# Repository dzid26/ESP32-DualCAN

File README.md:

# ESP32-DualCAN - aka Dorky Commander
Open source alternative to S3XY Commander with Molex connector compatible with Enhauto harnesses.

ESP32-C6 functions: 
- Dual CAN
- BLE for WebUI, OTA and TeslaBLE
- WiFi (file browser)
- USB-C for development (flashing, debugging)

See [`hardware/README.md`](hardware/README.md) for detailed spec and schematics.

## Flash the firmware

### Option A: Web UI (wireless OTA update)

1. Connect via BLE (see [Connect over BLE](#connect-over-ble)).
2. Go to **Settings → Firmware** in the [Dorky Commander web UI](https://opencartools.github.io/ESP32-DualCAN/).
3. Click **Upload .bin** and select a firmware `.bin` from disk (download from [GitHub Releases](https://github.com/opencartools/ESP32-DualCAN/releases) if needed).
4. The progress bar shows transfer status. The device reboots automatically when done.

### Option B: USB

**Download prebuilt binary:**

1. Download the latest `dorky-commander-vX.Y.Z.bin` from [GitHub Releases](https://github.com/opencartools/ESP32-DualCAN/releases).
2. Connect the board via USB-C. Easiest: open the [Espressif Web Flasher](https://espressif.github.io/esptool-js/) in Chrome and flash the `.bin` — no install needed.

   CLI alternative:

   ```bash
   pip install esptool
   esptool.py --chip esp32c6 write_flash 0x10000 dorky-commander-vX.Y.Z.bin
   ```

To build from source, see [firmware/README.md — Development — Build & Flash](firmware/README.md#build--flash) (PlatformIO extension recommended).

---

## Connect over BLE

1. Open the [Dorky Commander web UI](https://opencartools.github.io/ESP32-DualCAN/) in Chrome.
   *(Or install it as an app: Settings → Install app → Add to home screen.)*
2. Click **Connect** in the status bar.
3. Select **Dorky Commander** from the Bluetooth pairing dialog.
4. The status bar turns green and shows the firmware version.

> [!NOTE]
> The board advertises as `Dorky Commander`. Once paired, the pairing window stays closed for security — new devices cannot pair until you re-open it with a short-press of the B button or from the web UI on a bonded device (**Settings → Bluetooth → Open pairing window**). 

### "B" button — Bluetooth / Factory Reset

| Press | Action |
|---|---|
| Short press — release within 15 s | Open BLE pairing window for 60 s - see below |
| Hold ≥15 s | Factory reset — wipes BLE bonds, credentials, and scripts |
| Hold on Reset | ESP32 boot mode (advanced) |

## "R" button - Reset

ESP32 reset.

> [!TIP]
> If the board will be hidden behind car trim, pair with at least two devices (e.g., phone + laptop) — this avoids needing to reach the button, in case you loose a bond with the device.

See [docs/ble.md](docs/ble.md) for the full flow and troubleshooting.

---

## Choose your car

The board needs signal definitions (CAN dbc) to interpret signal `DI_vehicleSpeed` to raw IDs.

- Click the **car icon** in the top status bar and pick your vehicle (e.g., Tesla Model 3/Y). The matching DBC(s) load automatically.
- Or open **Gallery → DBCs** and click **Load** on the card for your car (choose **Bus 0** or **Bus 1** with the selector on the card if needed).
- For a custom file, open **DBC** in the left rail and click **Upload .dbc** — use the **Bus 0 / Bus 1** tabs at the top to view what's loaded for each bus.

The browser keeps the DBC locally in the browser for autocomplete and for preprocessing signal names into numeric IDs when you save a script. Verify with the search box in the DBC view.

---

## Install a script

1. Open **Gallery** in the left rail → **Scripts** tab.
2. Find **Hello log** and click **Install** — it opens **Automations** with the file preloaded (or use **Automations → Load… → Hello log**).
3. Click **Save & enable** (or **Save** then toggle). The file appears in the **Installed** list on the left; the switch shows enabled/disabled. Use **Revert** to discard edits.
4. With the script enabled, open **Log** (left rail, bottom) — you should see `hello_log: setup` followed by `heartbeat` every 5 s. `print()` from the board streams there over BLE; no CAN connection required.

5. Next, try more useful script from the **Gallery** — browse **Gallery → Scripts** for real-car automations like *Easy entry window drop*, or *Light flash → horn beep*, or pick a DBC in **Gallery → DBCs**.

---

## Use action tiles

1. Open **Gallery** in the left rail → **Scripts** tab.
2. Find **Tesla fold mirrors** and click **Install** — it opens **Automations** with `tesla_fold_mirror_tile.be` preloaded. Click **Save & enable**.
3. Return to **Dashboard**: two tiles appear — `fold_mirrors` and `unfold_mirrors`.
4. Tap a tile — the mirrors fold/unfold and the LED blinks blue. Requires Tesla Model 3/Y DBC on Bus 0 and the car awake.

## Use AI edit to write simple scripts

No coding needed — describe what you want in plain English.

1. One-time setup: Open **Settings → AI assistant** and paste your Anthropic API key — **BYOK** (Bring Your Own Key, billed to your Anthropic account). The key is stored locally in your browser and, if you click **Save to device**, also on the Dorky Commander non-volatile-storage - so any paired browser can reuse it. The browser calls Anthropic directly (`api.anthropic.com`); the key is never shared - it stays with you.

2. **Option A — from a script:** Open **Automations**, then click **AI edit** (sparkle icon) on any script. It opens **AI assistant** with that file attached as context — just type what to change.
   **Option B — from scratch:** Open **AI assistant** in the left rail directly and type a request, e.g., `Print battery temperature to log panel`

3. Press **Send** (`Ctrl/Cmd+Enter`). The assistant streams a `berry` code block (knowing your loaded DBC signals) with a proper `# @name` and `def setup()`.

4. Click **Install & enable** on the code card — it saves as `ai_script_*.be` and enables it. Check **Log** for `print()` output or **Dashboard** if it registered an action tile.

> [!TIP]
> Load a CAN definitions first (Choose your car) — the AI sees the first ~80 signal names from the browser and will use exact `message_name` / `signal_name` in `msg_sig_get`.

---

## Write your own scripts

Ready to go beyond examples?

- In **Automations**, click **Scripting Guide** (top bar, next to **New** / **Load…**) — it opens `docs/scripting.md` inside the UI with the full Berry API, CAN/DBC, timers, actions, LED, and `state_*` storage, plus a syntax cheat sheet. No tab switching needed. Point your AI agents to `docs/scripting.md` to help you out.

Start small: copy a Gallery script, tweak it in the editor, **Save & enable**, and watch **Log**.

---

## Development

### Brand scripting — adding scripts to the Gallery

See [`scripts/README.md`](scripts/README.md) for the full guide — Gallery pulls from `scripts/<brand>/*.be` at npm build time (`import.meta.glob`). Create `scripts/<brand>/your_script.be` with `# @name` / `# @description` / `# @bus` file header, implement `def setup()`, and verify in **Gallery → Scripts → Install**.

### Firmware

See [firmware/README.md — Development](firmware/README.md#development) for build, flash, and test instructions. Recommended: [PlatformIO IDE extension for VS Code](https://platformio.org/install).

### Web UI

First time
```bash
cd webui
npm install
```
Then
```
npm run dev   # open http://localhost:5173
```

Requires [Node.js](https://nodejs.org/).

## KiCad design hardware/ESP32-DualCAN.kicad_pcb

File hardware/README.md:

# Hardware — ESP32-DualCAN

## Characteristics
- 9-58 V operating range (e.g. Cybertruck),
- 5V rail: 0.5A continuous at room temp
- Dual CAN
- integrated 2.4 GHz antenna
- RGB LED
- USB-C - USB CDC (virtual COM, debugging)  

## Case
Designed in FreeCAD
- size 23.5 x 42.8 x 12.3 mm

## ICs
- ESP32-C6-Zero (ESP32-C6FH8, 8MB, BLE + WiFi, 2x TWAI CAN2.0 controllers)
- 2x CAN transceivers TCAN1044
- TI LV2862 DC/DC converter

## PCB
Designed in Kicad
- size 19.5 x 41.5 mm

## Images
- ESP32-C6-Zero chiplet and Molex connector:

- On the other side there are components and optional pads to solder cables with a female [connector](https://duckduckgo.com/?q=MX2.54+cable+6p) to daisy chain with s3xy buttons or a strip:

- It can accommodate optional female 2.54mm headers for custom extensions:

## Schematic

Source files: [`ESP32-DualCAN.kicad_sch`](ESP32-DualCAN.kicad_sch), [`ESP32-DualCAN.kicad_pcb`](ESP32-DualCAN.kicad_pcb) — see [KiCad-Waveshare-ESP32/](KiCad-Waveshare-ESP32/) for the ESP32-C6-Zero module footprint.

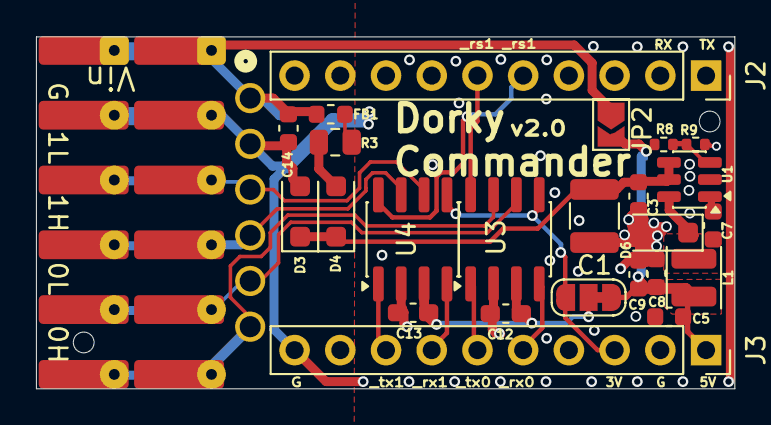
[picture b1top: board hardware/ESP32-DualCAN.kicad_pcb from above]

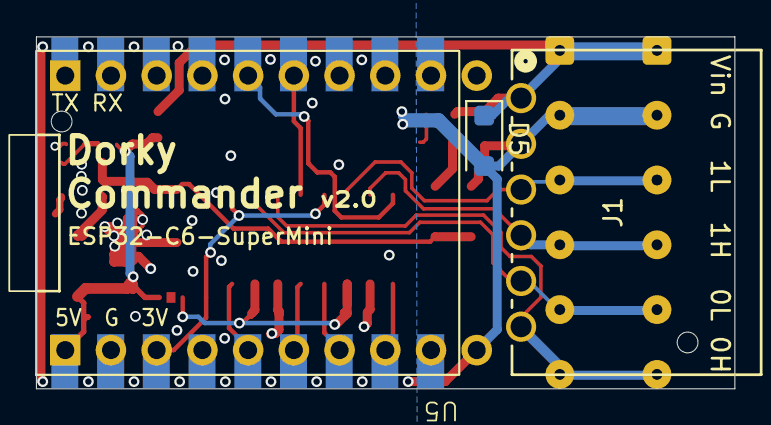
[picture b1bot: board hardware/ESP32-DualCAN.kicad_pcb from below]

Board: 2 copper layers, 38.8 x 19.6 mm, 31 parts (3 on the bottom side), 30 nets.

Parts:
C1: 10u 100v; C_1210_3225Metric
C3, C14: 100n 100V; C_0603_1608Metric
C5, C9: 22u; C_0603_1608Metric
C7, C8: 100n; C_0603_1608Metric
C12, C13: 100n; C_0603_1608Metric_Pad1.08x0.95mm_HandSolder
D3, D6: DSK38; D_SOD-123F
D4: SMF58A; D_SOD-123F
D5: SMF30CA; D_SOD-123F
FB1: FerriteBead; L_0603_1608Metric
J1: Molex 70553 6p; CONN_705530005_06_MOL
J2, J3: Conn_01x10_Socket; PinSocket_1x10_P2.54mm_Vertical
J4, J6: holes; SolderWire-0.1sqmm_1x06_P3.6mm_D0.4mm_OD1mm
J5, J7: pads; SolderWire-0.1sqmm_1x06_P3.6mm_D0.4mm_OD1mm
JP1: SolderJumper_3_Bridged12; SolderJumper-3_P1.3mm_Bridged12_RoundedPad1.0x1.5mm_NumberL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
JP2: SolderJumper_2_Open; SolderJumper-2_P1.3mm_Open_TrianglePad1.0x1.5mm
L1: 22uH; L_Changjiang_FTC322520S
R3: 1ohm; R_0805_2012Metric
R8: 56k; R_0402_1005Metric
R9: 10k; R_0402_1005Metric
U1: MLMR16006Y; TSOT-23-6
U3, U4: TCAN1044AV; SOIC-8_3.9x4.9mm_P1.27mm
U5: ESP32-C6-Zero; Waveshare-ESP32-C6-Zero

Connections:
+3.3V: J3.3, JP1.3 (B), U3.5 (VIO), U4.5 (VIO), U5.3 (V3V)
+BATT: C14.1, D5.1 (A1), FB1.1, J1.1, J4.1, J5.1, J6.1, J7.1, JP2.1 (A)
/BATT_Diode: C1.1, C3.1, D3.1 (K), D4.1 (A1), U1.4 (EN), U1.5 (VIN)
CAN0_H: J1.6, J4.6, J5.6, J6.6, J7.6, U3.7 (CANH)
CAN0_L: J1.5, J4.5, J5.5, J6.5, J7.5, U3.6 (CANL)
CAN0_RS: J2.6, U3.8 (STB), U5.13 (IO19)
CAN0_RXD: J3.5, U3.4 (RXD), U5.5 (IO1)
CAN0_TXD: J3.6, U3.1 (TXD), U5.6 (IO2)
CAN1_H: J1.4, J4.4, J5.4, J6.4, J7.4, U4.7 (CANH)
CAN1_L: J1.3, J4.3, J5.3, J6.3, J7.3, U4.6 (CANL)
CAN1_RS: J2.5, U4.8 (STB), U5.14 (IO18)
CAN1_RXD: J3.7, U4.4 (RXD), U5.7 (IO3)
CAN1_TXD: J3.8, U4.1 (TXD), U5.8 (IO4)
GND: C1.2, C3.2, C5.2, C8.2, C9.2, C12.2, C13.2, C14.2, D4.2 (A2), D5.2 (A2), D6.2 (A), J1.2, J3.2, J3.10, J4.2, J5.2, J6.2, J7.2, R9.1, U1.2 (GND), U3.2 (GND), U4.2 (GND), U5.2 (GND)
unnamed: D3.2 (A), R3.2
unnamed: C7.2, D6.1 (K), L1.1, U1.6 (SW)
unnamed: FB1.2, R3.1
unnamed: J2.1, U5.18 (TX)
unnamed: J2.2, U5.17 (RX)
unnamed: J2.3, U5.16 (IO14)
unnamed: J2.4, U5.15 (IO15)
unnamed: J2.7, U5.12 (IO20)
unnamed: J2.8, U5.11 (IO21)
unnamed: J2.9, U5.10 (IO22)
unnamed: J3.4, U5.4 (IO0)
unnamed: J3.9, U5.9 (IO5)
unnamed: C12.1, C13.1, JP1.2 (C), U3.3 (VCC), U4.3 (VCC)
unnamed: C7.1, U1.1 (BOOST)
unnamed: R8.1, R9.2, U1.3 (FB)
VCC: C5.1, C8.1, C9.1, J3.1, JP1.1 (A), JP2.2 (B), L1.2, R8.2, U5.1 (VCC)

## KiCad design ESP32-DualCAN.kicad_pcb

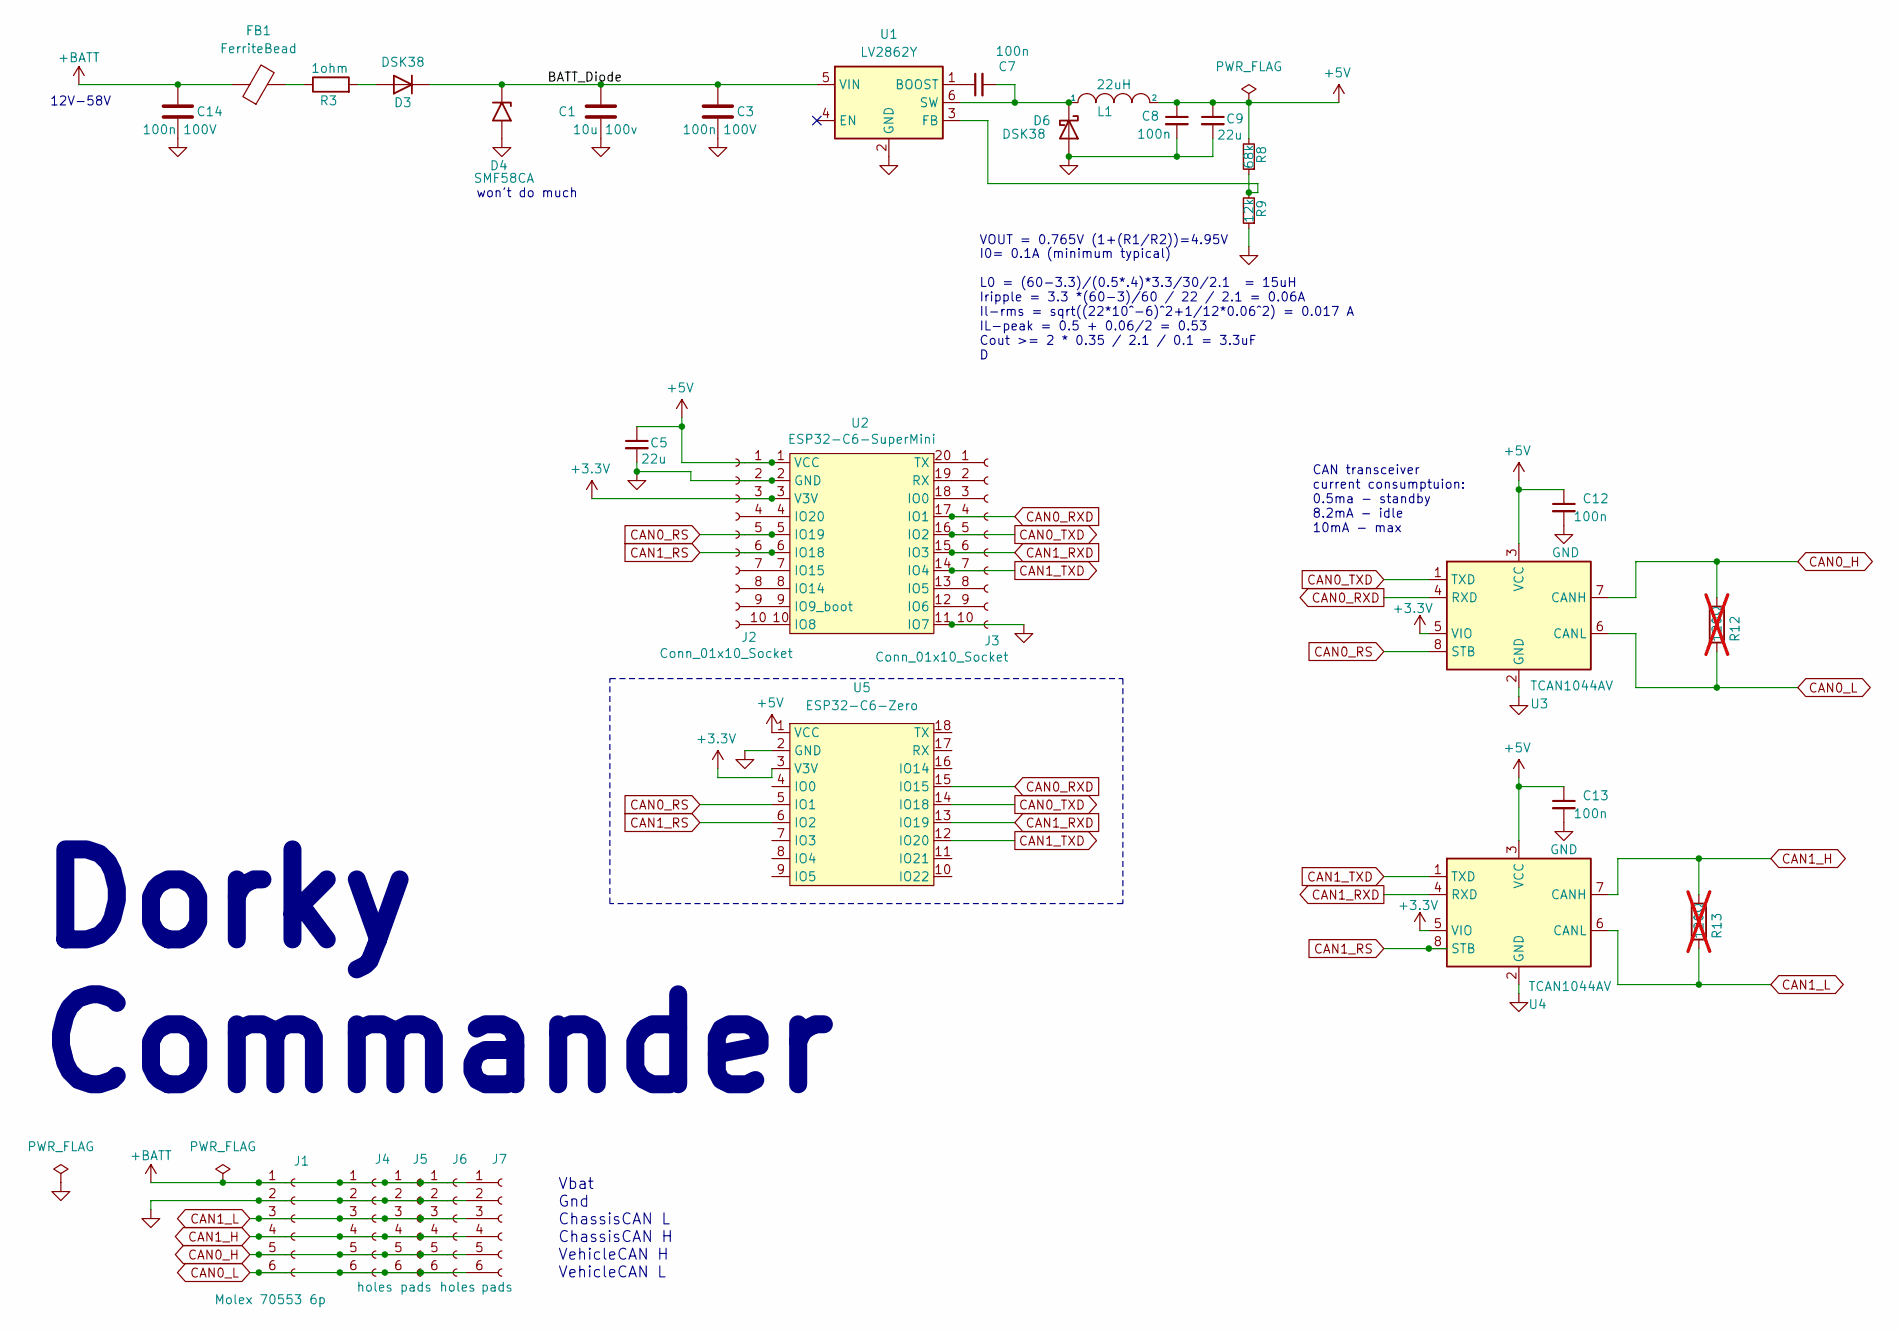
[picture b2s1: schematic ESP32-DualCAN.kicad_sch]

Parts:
C1: 10u 100v; C_1210_3225Metric; LCSC C576517
C3, C14: 100n 100V; C_0805_2012Metric; LCSC C28233
C5, C9: 22u; C_0603_1608Metric; LCSC C59461
C7, C8, C12, C13: 100n; C_0402_1005Metric; LCSC C1525
D3, D6: DSK38; D_SOD-123F; LCSC DSK38
D4: SMF58CA; D_SOD-123F; LCSC C42371753
FB1: FerriteBead; L_0603_1608Metric; LCSC C14709
J1: Molex 70553 6p; CONN_705530005_06_MOL; LCSC C505298
J2, J3: Conn_01x10_Socket; PinSocket_1x10_P2.54mm_Vertical; LCSC C2905418
J4, J6: holes; SolderWire-0.1sqmm_1x06_P3.6mm_D0.4mm_OD1mm
J5, J7: pads
L1: 22uH; L_Changjiang_FTC322520S; LCSC C5832391
R3: 1ohm; R_0805_2012Metric; LCSC Part # C25271
R8: 68k; R_0402_1005Metric; LCSC C36871
R9: 12k; R_0402_1005Metric; LCSC C25752
R12, R13: 120Ω; R_1206_3216Metric_Pad1.30x1.75mm_HandSolder; LCSC C17909; not fitted
U1: LV2862Y; TSOT-23-6; LCSC C3193152
U2: ESP32-C6-SuperMini
U3, U4: TCAN1044AV; SOIC-8_3.9x4.9mm_P1.27mm; LCSC C3234993
U5: ESP32-C6-Zero; Waveshare-ESP32-C6-Zero

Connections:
+3.3V: J2.3, U2.3 (V3V), U3.5 (VIO), U4.5 (VIO), U5.3 (V3V)
+5V: C5.1, C8.1, C9.1, C12.1, C13.1, J2.1, L1.2, R8.2, U2.1 (VCC), U3.3 (VCC), U4.3 (VCC), U5.1 (VCC)
+BATT: C14.1, FB1.1, J1.1, J4.1, J5.1, J6.1, J7.1
/BATT_Diode: C1.1, C3.1, D3.1 (K), D4.1 (A1), U1.5 (VIN)
CAN0_H: J1.5, J4.5, J5.5, J6.5, J7.5, R12.1, U3.7 (CANH)
CAN0_L: J1.6, J4.6, J5.6, J6.6, J7.6, R12.2, U3.6 (CANL)
CAN0_RS: J2.5, U2.5 (IO19), U3.8 (STB), U5.5 (IO1)
CAN0_RXD: J3.4, U2.17 (IO1), U3.4 (RXD), U5.15 (IO15)
CAN0_TXD: J3.5, U2.16 (IO2), U3.1 (TXD), U5.14 (IO18)
CAN1_H: J1.4, J4.4, J5.4, J6.4, J7.4, R13.1, U4.7 (CANH)
CAN1_L: J1.3, J4.3, J5.3, J6.3, J7.3, R13.2, U4.6 (CANL)
CAN1_RS: J2.6, U2.6 (IO18), U4.8 (STB), U5.6 (IO2)
CAN1_RXD: J3.6, U2.15 (IO3), U4.4 (RXD), U5.13 (IO19)
CAN1_TXD: J3.7, U2.14 (IO4), U4.1 (TXD), U5.12 (IO20)
GND: C1.2, C3.2, C5.2, C8.2, C9.2, C12.2, C13.2, C14.2, D4.2 (A2), D6.2 (A), J1.2, J2.2, J3.10, J4.2, J5.2, J6.2, J7.2, R9.1, U1.2 (GND), U2.2 (GND), U2.11 (IO7), U3.2 (GND), U4.2 (GND), U5.2 (GND)
unnamed: D3.2 (A), R3.2
unnamed: C7.2, D6.1 (K), L1.1, U1.6 (SW)
unnamed: FB1.2, R3.1
unnamed: J2.4, U2.4 (IO20)
unnamed: J2.7, U2.7 (IO15)
unnamed: J2.8, U2.8 (IO14)
unnamed: J2.9, U2.9 (IO9_boot)
unnamed: J2.10, U2.10 (IO8)
unnamed: J3.1, U2.20 (TX)
unnamed: J3.2, U2.19 (RX)
unnamed: J3.3, U2.18 (IO0)
unnamed: J3.8, U2.13 (IO5)
unnamed: J3.9, U2.12 (IO6)
unnamed: C7.1, U1.1 (BOOST)
unnamed: R8.1, R9.2, U1.3 (FB)

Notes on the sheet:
12V-58V
won't do much
Vbat Gnd ChassisCAN L ChassisCAN H VehicleCAN H VehicleCAN L
Dorky Commander
CAN transceiver current consumptuion: 0.5ma - standby 8.2mA - idle 10mA - max
VOUT = 0.765V (1+(R1/R2))=4.95V
I0= 0.1A (minimum typical) L0 = (60-3.3)/(0.5*.4)*3.3/30/2.1 = 15uH Iripple = 3.3 *(60-3)/60 / 22 / 2.1 = 0.06A Il-rms = sqrt((22*10^-6)^2+1/12*0.06^2) = 0.017 A IL-peak = 0.5 + 0.06/2 = 0.53 Cout >= 2 * 0.35 / 2.1 / 0.1 = 3.3uF D

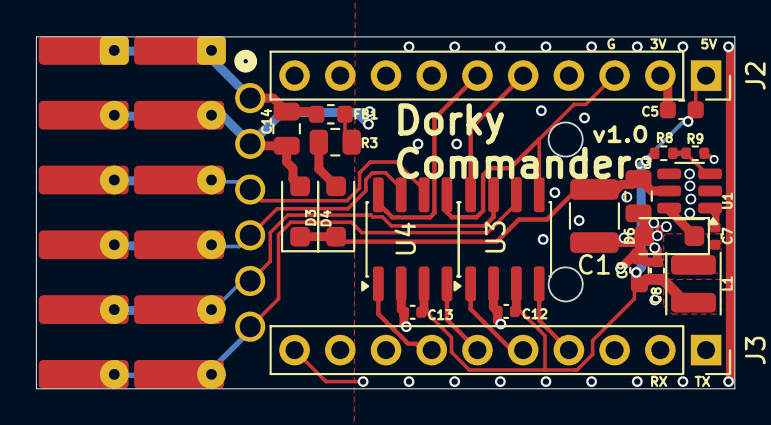
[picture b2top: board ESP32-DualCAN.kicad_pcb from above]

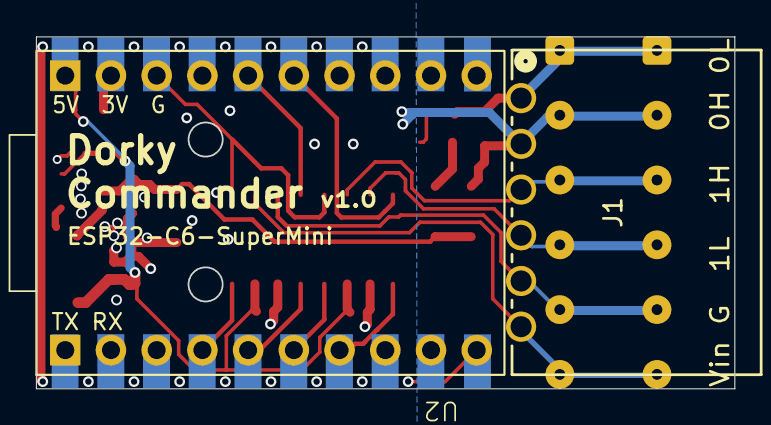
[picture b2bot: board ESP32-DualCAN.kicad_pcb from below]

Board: 2 copper layers, 38.8 x 19.6 mm, 28 parts (2 on the bottom side), 30 nets.

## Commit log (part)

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2026-05-12 Revert "fix(webui): remove filename input from editor header; lower sparkle icon"
    This reverts commit a93024d0161ef15680f8020155735c3b55970098.
2026-05-12 narrow sim/kill
2026-05-13 bits ui enable toggles
2026-05-16 can bitrate setting
2026-05-16 fixes status
2026-05-18 Fix duplicate BLE disconnect toasts
2026-05-18 Allow text selection in ble toast notifications
2026-05-18 fix: flipped VehicleCAN pins
2026-05-18 docs(ble): inline USB cable recovery commands; delete maintenance.md
    maintenance.md deleted.
2026-05-18 can silk on top
2026-05-18 Ignore local history folders
2026-05-18 docs: no periodic messages needed
2026-05-18 example: Tesla flash hazards
2026-05-19 feat(dbc): add DI_speed, UI_vehicleControl, UI_powertrainControl to embedded DBC
    The embedded vehicle DBC previously had only 11 messages. The mirror-fold
    and track-mode scripts referenced messages that were absent, so
    can_msg_get always returned nil and no TX frame was ever sent.
    Add three message definitions to tesla_model3_vehicle.dbc:
    DI_speed (599) — DI_vehicleSpeed for speed reading
    UI_vehicleControl (627) — UI_mirrorFoldRequest, UI_honkHorn, etc.
2026-05-21 Revert "narrow sim/kill"
    This reverts commit 54d0a7c80af559288b65844dd43b74ad1d668dd7.
2026-05-21 dont spam toast on cancel
2026-05-21 dont mix bridging
2026-05-22 actually instantiate the list class. Now we can read the frame
2026-05-30 feat: add smart autoscroll to log pane
    - Auto-scroll to bottom on new log entries
    - Lock at bottom when at the bottom, unlock when scrolling up
    - Add scroll-to-bottom button between Clear and Close buttons
2026-05-30 auto-open log panel on error, blink icon on warning
2026-05-30 Add layered error codes for DBC and CAN lookup failures
    DBC layer (dbc_pack.h):
    DBC_ERR_NO_SIG (-101) — signal name not found
    DBC_ERR_NO_MSG (-102) — message name not found
    CAN layer (can.h):
    CAN_DBC_ERR (-201) — DBC lookup failed (wraps both DBC misses)
    CAN_ERR_FULL (-202) — callback registry full
2026-05-30 ScriptsView: restore last-opened script + scroll pos across tab switches
    - Persist last-opened script filename in localStorage (dc-last-script)
    - Remember scroll position per script in AppState Map (survives tab switch)
    - Add scrollTop binding to CodeMirrorEditor for bidirectional sync
    - Use mounted guard to prevent double refresh() race on mount
    - Save scroll position in onDestroy so tab switch captures it
2026-05-30 ble: guard against duplicate gattserverdisconnected on Windows
    Windows Web Bluetooth can fire the disconnect event twice for a single
    disconnect. The second call sees userInitiatedDisconnect already reset
    to false and misclassifies it as 'unexpected', triggering a misleading
    toast. Track handled disconnects to skip duplicates.
2026-05-30 Keep all views mounted, hide inactive ones via display:none
    Replaces the {#if}/{:else if} destroy/recreate pattern with
    always-mounted div wrappers toggling display:none. Component
    state (selected script, editor content, scroll position) now
    survives tab switches naturally, removing the need for the
    mounted guard, onDestroy scroll save, and store scroll map.
2026-05-30 Add CHECK_ARITY + CHECK_TYPE macros to all Berry bindings
    - Define CHECK_TYPE (type assertion with be_typename) and CHECK_ARITY
    (argument count check) macros at top of file
    - Move all #define constants (MAX_BERRY_CBS, MAX_TIMERS, MAX_ACTIONS,
    ACTION_NAME_MAX) to the top
    - Convert all 19 Berry binding functions from silent nil-return on
    type/arity mismatch to explicit type_error raises via macros
2026-05-30 Fix show/hide layout: wrapper divs need flex:1 when visible
    Active wrapper divs now use 'flex: 1; display: flex; flex-direction:
    column; min-height: 0' so views fill the available space instead of
    collapsing vertically. Also removed the ResizeObserver hack from
    CodeMirrorEditor — it caused layout jumps and the scrollbar issue
    was actually due to the missing flex sizing.
    DashboardView: refresh action list when tab becomes visible
2026-05-30 ui: add reboot toast and suppress unexpected disconnect during reboot/ota
2026-05-30 Configure commentTokens on Berry parser so Ctrl+/ toggles line comments
2026-05-30 DashboardView: error decorator on tiles that failed to run
    When invokeAction rejects, the tile shows a red border/outline and
    an 'error' label in the footer. Hovering the tile shows the error
    message as its title. The error clears when the tile is fired again.
2026-05-30 dev: add host + tunnel scripts, allow all hosts for tunnelmole
2026-05-30 dbc: widen name_off to uint32_t, sig_count to uint16_t for large DBC support
    The Tesla Model 3/Y dedup DBC (403 messages, 8881 signals) pushes
    the string table past 64 KiB, overflowing uint16_t name_off.
    Several messages also exceed 255 signals, requiring uint8_t -> uint16_t.
    Breaking binary format change — DBC_VERSION bumped to 2.
    - dbc_types.h: name_off uint32_t, sig_count uint16_t, version 2
    - dbc_pack.h: dbc_str() parameter uint32_t
2026-05-30 ble: reorder setupDevice - listener after I/O, setConnected after notifs (fix stale events + Android GATT conflict)
2026-05-31 http file server
2026-05-31 refactor: extract berry completions/hover/context into berry-completions.ts
    - Move DBC-aware autocomplete, context detection (findContext, findDbcCall),
    Berry API bindings, keyword list, and berryHover into dedicated module
    - Add filterText to DBC completions so quoted labels match unquoted typing
    - Fix scroll sync: ResizeObserver replaces broken (hidden editors)
    - Comments now show DBC name completions
    - Berry API functions only proposed at statement start
2026-05-31 parsed dbc caching and parallel loading
2026-05-31 private DBC per car, fix log, remove load Tesla button
2026-06-01 protocol: reset rxBuf and reject pending on disconnect
    Clears stale buffer data and pending promises so reconnection
    starts with a clean state instead of corrupting frame parsing.
2026-06-01 webui: auto-recover from stalled BLE notification stream
    The Web Bluetooth notification stream (characteristicvaluechanged) can
    silently stop firing on some platforms while the GATT connection appears
    healthy. Writes still reach the firmware but response notifications are
    never delivered, causing every protocol call to time out.
    - Protocol tracks lastRxTimestamp; fires onStall() once when a call()
    timeout detects no data received for >10s while connected.
2026-06-01 fix type errors: remove lastUploadedBus references, fix target null check, use valid icon name
2026-06-01 refresh scripts state when entering the script view
2026-06-01 dont reset on serial monitor open
2026-06-01 clip ble logs on connect; add getLogLevel; suppress NimBLE via sdkconfig
    - esp_log_level_set('ble', ESP_LOG_WARN) now runs on BLE connect
    (not boot), so serial monitor stays verbose when no client connected
    - handle_log_set_level re-applies ble clip on tag='*' changes
    - add getLogLevel() handler + protocol.ts getLogLevel() call
    - store.svelte.ts syncs dropdown from firmware on connect
    - sdkconfig.defaults: CONFIG_BT_NIMBLE_LOG_LEVEL_ERROR=y,
2026-06-01 add Radio view with Perchance generator iframe
    - new RadioView.svelte with iframe to null.perchance.org/radio-box-2-lite
    - register 'radio' ViewId in store.svelte.ts
    - add radio icon (rectangle + antenna + speaker + grill) to icons.ts
    - add Radio nav item in nav.ts (Fun group)
    - wire up in App.svelte
2026-06-01 add hash-based view routing (#view-id links)
2026-06-04 add signal & message search to DBC view
    - Search bar with debounced input (120ms) for smooth typing
    - Filters both message names and signal names in real time
    - Auto-expand when <20 results, auto-collapse on clear
    - Matching text highlighted in signal names
    - Per-message match count in header
    - Empty state when no matches
2026-06-04 fix(webui): mobile editor fills viewport, toolbar no longer overflows
2026-06-06 fix l_can_msg_get map instantiation
    Problem: be_newobject(vm, "map") at firmware/src/scripting/berry_bindings.c:432,462 unwraps .p and returns a raw BE_MAP, but Berry's GETIDX/SETIDX VM opcodes only work on instances (BE_INSTANCE). Thi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
    Fix (pattern from commit baafd7d5 and Berry FFI docs (https://berry.readthedocs.io/en/latest/source/en/FFI-Example.html#instantiate-a-list-object-in-a-native-function)):
2026-06-06 add berry can_msg_new to create empty message draft - ready to be filled with actual data.
2026-06-07 use tabs for showing preprocessed
2026-06-07 Restore script state on Save - Remove Save and Enable
2026-06-07 link scripting.md
2026-06-08 separate berry highlighting tokenizer
2026-06-08 fix svelte-check warnings in LogPane.svelte
    Wrap .log-link CSS in :global() for {@html} content. Add role=button + tabindex + onkeydown for a11y click-handler compliance. npm run check now 0 errors, 0 warnings.
2026-06-08 fix npm check
2026-06-08 Fix editor horizontal scrolling and script list not visible on narrow screens
2026-06-08 Shrink Scripting guide button
2026-06-08 view rail list not scrollable
2026-06-09 shift tab underscore
2026-06-09 Show installed bep if file not unsaved
2026-06-09 Red error line hihglighting. Dont scroll whole view when navigating to error line.
2026-06-09 fix error link hyperlink - remove leading space
2026-06-09 preview/installed watermark and dont blink the cursor
2026-06-09 no wrap in the guide tables
2026-06-09 fix guide code section rendering
2026-06-09 database icon for DBC
2026-06-09 vscode recomended extensions
2026-06-09 avoid trunkating file server file list names
2026-06-10 highlight berry builtins
2026-06-11 BE_DEBUG
2026-06-19 can_msg_new - dont specify bus for draft message. Specify bus for can_msg_get can_msg_send — swapped arg order from (draft, bus) to (bus, draft)
2026-06-19 read single message data can_recv_raw(bus, msg_id)
2026-06-20 fix: the esp32 web interface provides full device co... in AIView.svelte
    The ESP32 web interface provides full device control including Berry script execution, CAN bus message sending, and DBC file management without any authentication mechanism
2026-06-22 Store messages in a cache for ids that were attempted to be read
2026-06-23 Error traceback line number for timers and events
2026-06-24 Less noisy info log
2026-06-24 Log/display error lines once
2026-06-24 Adjustable log pane height
2026-06-25 fix windows native test
2026-06-26 Brought back Save and Enable
    This reverts commit 96775fbfa25fdcb776de5ce81af6d21be444efd5.
2026-06-26 ctrl shift z to redo
2026-06-26 cache_read optimization
2026-06-27 always regenerate bep
2026-06-27 store msg timestamp
2026-06-27 Rename signal_decode/signal_encode to msg_sig_get/msg_sig_set, fix draft data access via .p
    - Replace bytes-based l_signal_decode/l_signal_encode with draft-based
    l_msg_sig_get/l_msg_sig_set that read/write draft['.p']['data'] via
    Berry's canonical .p + getindex pattern (same as be_maplib.c).
    - Update preprocessor (preprocessor.ts) to emit msg_sig_get/msg_sig_set
    with inline metadata instead of signal_decode/signal_encode.
    - Update parse_check.c BINDING_NAMES: move msg_sig_get/msg_sig_set to
2026-06-28 Fix can_msg_send: read id/dlc/data from .p hidden member
    Map class instances store fields in .p (internal map). be_getmember
    silently fails on map instances, returning nil → id=0, dlc=0 sent.
    Use the same be_getmember('.p') + be_getindex('key') pattern as
    msg_sig_get/msg_sig_set and Berry's own be_maplib.c.
2026-06-28 Improve loopback test: verify can_msg_send wire output via CAN RX
    - After each can_msg_send, read back the looped-back frame via
    can_recv_raw(bus, id, 50) and assert the received bytes match
    the draft's data payload.
    - Previously the test only checked msg_sig_set ↔ msg_sig_get
    consistency within a single draft object, silently accepting
    garbage on the wire (id=0, dlc=0 from the .p member bug).
2026-06-28 Add light_flash_horn_beep script
    When UI_vehicleControl3 lightFlashRequest transitions from 0 to
    non-zero (lock/unlock confirmation, mobile-app find, sentry alarm),
    pulse shortHornRequest for 200ms to also beep the horn.
2026-06-29 Check script api version in the UI
2026-06-29 autocomplete: scope signal completions by draft variable's message
    - Import buildVarToMsgMap from preprocessor to track which message a
    draft variable refers to (shared logic with preprocessor validation)
    - msg_sig_get/set arg1 now shows only signals from the tracked message
    - can_msg_get arg1 shows messages filtered by parsed bus number
    - findContext now correctly skips line comments (#) instead of treating
    any # as comment context (broke scoping in scripts with header comments)
